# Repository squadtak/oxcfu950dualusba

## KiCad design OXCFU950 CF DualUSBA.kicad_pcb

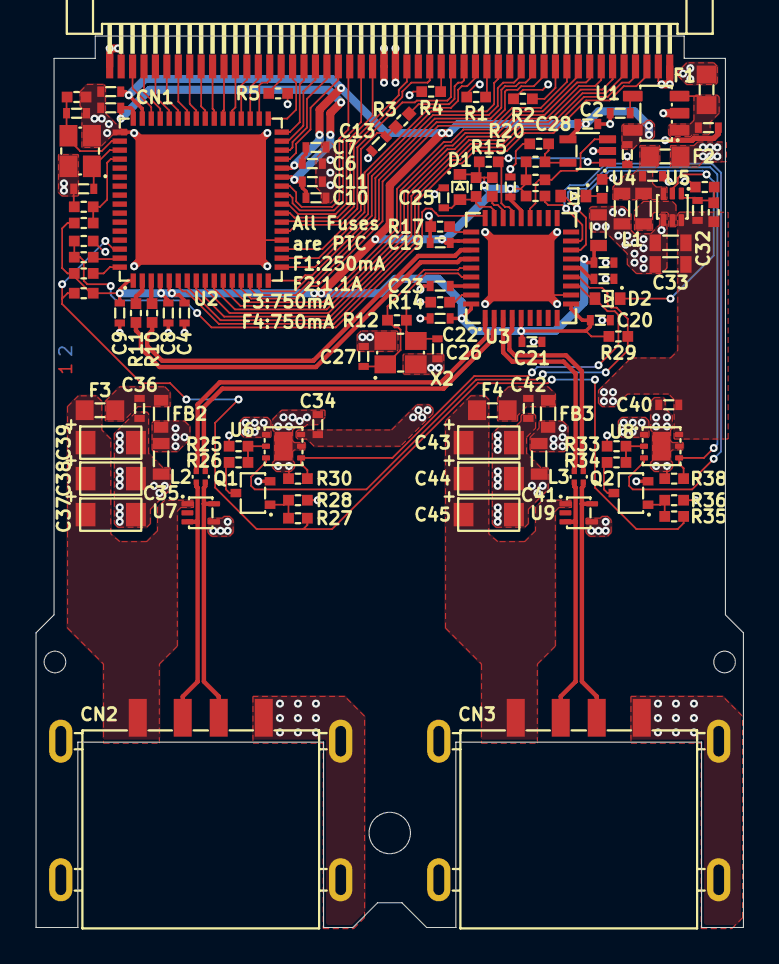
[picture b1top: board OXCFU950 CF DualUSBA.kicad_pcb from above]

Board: 2 copper layers, 39.3 x 49.5 mm, 111 parts (0 on the bottom side), 100 nets.

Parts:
C1, C3: 1u; C_0402
C2: 0.01u; C_0402
C4, C5, C8, C9, C12, C13, C16, C17, C19, C20, C21, C22, C23, C24, C25, C28, C30, C34, C36, C40, C42: 0.1u; C_0402
C6: 100p; C_0402
C7, C10: 4.7u; C_0402
C11: 1000p; C_0402
C14, C15, C26, C27: 12p; C_0402
C18: 4.7u; C_0603
C29, C32, C33, C35, C41: 10u; C_0603
C31: 1p; C_0402
C37, C38, C39, C43, C44, C45: 47u; C-TANTPOL_SMD_A08,I,S
CN1: CF_connector; CF_female_connector
CN2, CN3: 905-761A2022S10206
D1, D2, D3: BAT54X; SOD-523
F1: 0603L025/9XR; 0603
F2: 0603L110/12AR; 0603
F3, F4: 0603L075/8AR; 0603
FB2, FB3: BLM18PG121SN1D; FBEAD-SMD_0603
L1: PCT160808-R47-M; 0603
L2, L3: DLM0NSM900HY2D; DLM0NSxxxxxx2x
Q1, Q2: AO3400A; SOT-323
R1, R2, R3, R9, R13, R17, R18, R22, R24, R28, R29, R30, R36, R37, R38, R41: 100k; R_0402
R4, R5, R7, R8, R19, R20, R21: 0; R_0402
R6: 510k; R_0402
R10, R11: 33; R_0402
R12: 1M; R_0402
R14: 12k; R_0402
R15, R16, R42: 10k; R_0402
R23: 750k; R_0402
R25, R33: 680k; R_0402
R26, R34: 390k; R_0402
R27, R35: 510; R_0402
U1: TPS73133DBVR; SOT-23-5_DBV
U2: OXCFU950-QFAG; QFN-64_OXFORD
U3: USB2512BT/M2; SQFN-36_MICROCHIP_SMSC
U4: 24LC02BT-I/LT; SC-70-5_B4X,BAX,BZX,LT,LTY,8AX,BQX
U5: TPS61023DRLR; SOT-563_DRL
U6, U8: TPS25200DRVR; WSON-6_DRV
U7, U9: TPD2E001DRLR; SOT-23-5_DRL
X1: ECS-120-8-36-CKM-TR; ECX-2236xx
X2: ECS-240-8-36B2-CKM-TR; ECX-2236xx

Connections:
+1V8: C10.1, C11.1, C12.1, U2.27 (REG_VDD1V8), U2.48 (PLL_VDD1V8)
+3V3: C3.1, C4.1, C5.1, C6.1, C7.1, C8.1, C9.1, C16.1, C17.1, C18.1, C19.1, C20.1, C21.1, C22.1, C28.1, D1.1 (C), R7.1, R9.1, R13.1, R15.1, R16.1, R18.1, R19.1, R29.1, R37.1, R42.1, U1.5 (OUT), U2.1 (UART_VDD3V3), U2.4 (USB_VDD3V3), U2.5 (PCMCIA_VDD3V3), U2.28 (REG_VDD3V3), U2.47 (PCMCIA_VDD3V3), U3.5 (VDDA33), U3.10 (VDDA33), U3.15 (VDD33), U3.23 (VDD33), U3.29 (VDDA33), U3.36 (VDDA33), U4.4 (VCC)
/A0: CN1.20 (A0), U2.14 (A0)
/A1: CN1.19 (A1), U2.16 (A1)
/A2: CN1.18 (A2), U2.17 (A2)
/A3: CN1.17 (A3), U2.18 (A3)
/A4: CN1.16 (A4), U2.21 (A4)
/A5: CN1.15 (A5), U2.22 (A5)
/A6: CN1.14 (A6), U2.23 (A6)
/A7: CN1.12 (A7), U2.25 (A7)
/A8: CN1.11 (A8), U2.29 (A8)
/A9: CN1.10 (A9), U2.31 (A9)
/A10: CN1.8 (A10), U2.34 (A10)
/D0: CN1.21 (D0), U2.13 (D0)
/D1: CN1.22 (D1), U2.11 (D1)
/D2: CN1.23 (D2), U2.9 (D2)
/D3: CN1.2 (D3), U2.46 (D3)
/D4: CN1.3 (D4), U2.44 (D4)
/D5: CN1.4 (D5), U2.42 (D5)
/D6: CN1.5 (D6), U2.40 (D6)
/D7: CN1.6 (D7), U2.38 (D7)
/D8: CN1.47 (D8), U2.10 (D8)
/D9: CN1.48 (D9), U2.8 (D9)
/D10: CN1.49 (D10), U2.6 (D10)
/D11: CN1.27 (D11), U2.45 (D11)
/D12: CN1.28 (D12), U2.43 (D12)
/D13: CN1.29 (D13), U2.41 (D13)
/D14: CN1.30 (D14), U2.39 (D14)
/D15: CN1.31 (D15), U2.37 (D15)
/PRT1_OC: R29.2, U3.13 (OCS_N1), U6.3 (~FAULT)
/PRT1_PEN: D2.2 (A), R30.1, U3.12 (PRTPWR1/BC_EN1), U6.4 (EN)
/PRT2_OC: R37.2, U3.17 (OCS_N2), U8.3 (~FAULT)
/PRT2_PEN: D3.2 (A), R38.1, U3.16 (PRTPWR2/BC_EN2), U8.4 (EN)
/USB_1_DN: L2.4, U3.1 (USBDM_DN1/PRT_DIS_M1)
/USB_1_DP: L2.1, U3.2 (USBDP_DN1/PRT_DIS_P1)
/USB_1_OUT_DN: CN2.2 (D-), L2.3, U7.3 (IO1)
/USB_1_OUT_DP: CN2.3 (D+), L2.2, U7.5 (IO2)
/USB_2_DN: L3.4, U3.3 (USBDM_DN2/PRT_DIS_M2)
/USB_2_DP: L3.1, U3.4 (USBDP_DN2/PRT_DIS_P2)
/USB_2_OUT_DN: CN3.2 (D-), L3.3, U9.3 (IO1)
/USB_2_OUT_DP: CN3.3 (D+), L3.2, U9.5 (IO2)
/USB_DP: R11.1, U2.2 (USB_DP)
/USB_EN: R21.1, U2.63 (MIO2)
/USB_HIGHPOWER_EN: R27.1, R35.1, R42.2, U2.62 (MIO1)
/USB_UP_DN: R10.2, U3.30 (USBDM_UP)
/USB_UP_DP: R11.2, U3.31 (USBDP_UP)
GND: C1.2, C2.2, C3.2, C4.2, C5.2, C6.2, C7.2, C8.2, C9.2, C10.2, C11.2, C12.2, C13.2, C14.1, C15.1, C16.2, C17.2, C18.2, C19.2, C20.2, C21.2, C22.2, C23.2, C24.2, C25.2, C26.1, C27.1, C28.2, C29.2, C30.2, C32.2, C33.2, C34.2, C35.2, C36.2, C37.2, C38.2, C39.2, C40.2, C41.2, C42.2, C43.2, C44.2, C45.2, CN1.1 (GND), CN1.25 (-CD2), CN1.26 (-CD1), CN1.50 (GND), CN2.4 (GND), CN2.PAD (SHIELD), CN3.4 (GND), CN3.PAD (SHIELD), Q1.2 (S), Q2.2 (S), R4.2, R5.2, R6.1, R8.2, R14.2, R17.2, R20.2, R22.2, R24.2, R25.2, R28.2, R30.2, R33.2, R36.2, R38.2, R41.2, U1.2 (GND), U2.20 (TEST), U2.49 (PLL_VSS1V8), U2.PAD (VSS), U3.11 (TEST), U3.PAD (GND), U4.2 (VSS), U5.4 (GND), U6.5 (GND), U6.PAD, U7.4 (GND), U8.5 (GND), U8.PAD, U9.4 (GND), X1.PAD, X2.PAD
unnamed: C36.1, F3.1, FB2.2
unnamed: C42.1, F4.1, FB3.2
unnamed: CN1.7 (-CE1/-CS0), U2.36 (CE1#)
unnamed: CN1.32 (-CE2/-CS1), U2.35 (CE2#)
unnamed: CN1.34 (-IORD/-HDMARDY/HSTROBE), U2.32 (IORD#)
unnamed: CN1.35 (-IOWR/STOP), U2.30 (IOWR#)
unnamed: CN1.9 (-OE/-ATA_SEL), U2.33 (OE#)
unnamed: CN1.44 (-REG), U2.15 (REG#)
unnamed: CN1.33 (-VS1), R5.1
unnamed: CN1.40 (-VS2), R4.1
unnamed: CN1.42 (-WAIT/IORDY/-DDMARDY/DSTROBE), R1.2
unnamed: CN1.36 (-WE), U2.26 (WE#)
unnamed: CN1.24 (-WP/-IOIS16/-IOCS16), U2.7 (WP/IOIS16#)
unnamed: CN1.46 (BVD1/-STSCHG/-PDIAG), U2.12 (BVD1#/STSCHG#)
unnamed: CN1.45 (BVD2/-SPKR/-DASP), R2.2
unnamed: CN1.37 (READY/-IREQ/INTRQ), U2.24 (READY/IREQ#)
unnamed: CN1.41 (RESET/-RESET), R3.1
unnamed: C37.1, C38.1, C39.1, CN2.1 (VBUS), F3.2, U7.1 (VCC)
unnamed: C43.1, C44.1, C45.1, CN3.1 (VBUS), F4.2, U9.1 (VCC)
unnamed: C25.1, D1.2 (A), R13.2, U3.26 (RESET_N)
unnamed: D2.1 (C), D3.1 (C), R41.1, U5.2 (EN)
unnamed: Q1.3 (D), R26.2
unnamed: Q1.1 (G), R27.2, R28.1
unnamed: Q2.3 (D), R34.2
unnamed: Q2.1 (G), R35.2, R36.1
unnamed: C1.1, F1.2, U1.1 (IN), U1.3 (EN)
unnamed: C2.1, U1.4 (NB)
unnamed: C13.1, R3.2, U2.19 (RESET)
unnamed: R7.2, R8.1, U2.52 (CIS_MODE)
unnamed: R9.2, U2.64 (MIO3)
unnamed: R10.1, U2.3 (USB_DM)
unnamed: C14.2, R6.2, U2.50 (XTLI), X1.3
unnamed: C15.2, U2.51 (XTLO), X1.1
unnamed: C24.1, U3.14 (CRFILT)
unnamed: R18.2, U3.25 (HS_IND/CFG_SEL1)
unnamed: C23.1, U3.34 (PLLFILT)
unnamed: R14.1, U3.35 (RBIAS)
unnamed: R15.2, U3.24 (SCL/SMBCLK/CFG_SEL0), U4.1 (SCL)
unnamed: R16.2, U3.22 (SDA/SMBDATA/NON_REM1), U4.3 (SDA)
unnamed: R17.1, U3.28 (SUSP_IND/LOCAL_PWR/NON_REM0)
unnamed: R21.2, R22.1, U3.27 (VBUS_DET)
unnamed: C26.2, R12.1, U3.33 (XTALIN/CLKIN), X2.3
unnamed: C27.2, R12.2, U3.32 (XTALOUT), X2.1
unnamed: R19.2, R20.1, U4.5 (WP)
unnamed: C31.2, R23.2, R24.1, U5.1 (FB)
unnamed: L1.2, U5.5 (SW)
unnamed: C29.1, C30.1, F2.2, L1.1, U5.3 (VIN)
unnamed: R25.1, R26.1, U6.2 (ILIM)
unnamed: C35.1, FB2.1, U6.1 (OUT)
unnamed: R33.1, R34.1, U8.2 (ILIM)
unnamed: C41.1, FB3.1, U8.1 (OUT)
VBUS: C31.1, C32.1, C33.1, C34.1, C40.1, R23.1, U5.6 (VOUT), U6.6 (IN), U8.6 (IN)
VCC: CN1.13 (VCC), CN1.38 (VCC), F1.1, F2.1, R1.1, R2.1

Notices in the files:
OXCFU950 CF DualUSBA.kicad_pcb:
©2026 squad
